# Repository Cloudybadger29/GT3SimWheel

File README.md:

# Custom GT3 Sim Racing Steering Wheel

A project with custom CAD mechanical assembly, 3D printable modular enclosures and ergonomic grips, CNC-machined structural faceplate, integrated magnetic dual-paddle shifters with microswitches, and a custom diode-matrix carrier PCB designed for manual through-hole soldering.

---

## Project Overview

This project is a **GT3 Sim Racing Wheel** engineered for PC sim racing platforms (iRacing, Assetto Corsa Competizione, rFactor 2).

The project is currently in the **detailed engineering and design verification phase**:
- **Mechanical Design (CAD)**: Conceptualized and surfaced initially in **Autodesk Fusion**, then transitioned to **Dassault Systèmes SolidWorks** for assembly modeling and to follow industry standards.
- **Manufacturing Strategy (Planned)**: Hybrid build pairing a rigid CNC-milled structural front plate with 3D-printed modular grips, rear electronics housing, and structural spacer components.
- **Electronics & ECAD (In Progress)**: Custom carrier backplane currently being laid out in **KiCad EDA** around an ATmega32U4 controller, integrating anti-ghosting switching diodes and through-hole solder pads planned for manual assembly.
- **Shifter Subassembly**: Dual-action magnetic paddle units driven by high-reliability Omron microswitches.

*Note: All components are currently modeled in CAD/ECAD. Physical manufacturing and component sourcing will begin once the PCB layout is complete.*

---

## Media & Renders

| Isometric Assembly | Exploded CAD View |
| :---: | :---: |
|  |  |

| Rear & Paddle Assembly | Custom PCB Carrier (KiCad 3D) |
| :---: | :---: |
|  |  |

---

## Key Engineering Points

### 1. Mechanical Design & Manufacturing
- **CNC Structural Faceplate**: A rigid custom CNC-machined front plate designed to withstand high force-feedback torque loads from direct-drive wheelbases without chassis deflection.
- **3D Printing**: All enclosures, grip bodies, and mounting spacers will be 3D printed.
- **Two-Piece Modular Grips**: Split-shell hand grips which can be easily replaced and bolt securely through the faceplate using countersunk M5 hardware.
- **Standard Hub Pattern**: Integrated Moza ESR wheel bolt pattern allowing direct fitment to only the quick release on the Moza ESR Quick Release. Adapters between bolt patterns are widespread.

### 2. Dual-Paddle Magnetic Shifters
- **Actuation**: Integrated 8×3mm magnets give crisp, tactile snap-action return.
- **Sensors**: **Omron D2FC-F-7N** microswitches rated for high-cycle reliability and responsive shift registration.
- **Dual-Paddle Geometry**: Upper and lower paddles allow independent assignment (gear up/down plus secondary functions).

### 3. PCB & Electrical Design (In Design)
- **ECAD Tool**: Schematic capture and board layout in **KiCad EDA**.
- **Microcontroller**: Arduino Pro Micro footprint (ATmega32U4, 5V/16MHz) for native USB HID gamepad capabilities.
- **Assembly Plan**: Through-hole layout designed for precision hand soldering, featuring clearly labeled reference silk screens for components and leaded DO-35 diodes.
- **Ghosting-Free Diode Matrix**: Fast-switching 1N4148 diodes isolate each switch input to prevent crosstalk during simultaneous multi-button presses.
- **Inputs Supported**:
  - 10x PBS-33B momentary pushbuttons
  - 4x Omron D2FC-F-7N paddle microswitches
  - 2x KY-040 rotary encoders (for in-race TC, ABS, or brake-bias trim)
- **Central Pass-Through**: Custom clearance holes routed into the PCB matching the PCD wheelbase bolt circle.

---

## Exploded Assembly Breakdown

The mechanical stack consists of:
1. **Front Split Grips**: Ergonomically shaped front halves fastened with countersunk M5 bolts.
2. **Faceplate Controls**: 10x PBS-33B pushbuttons and 2x KY-040 rotary encoder shafts.
3. **CNC Front Faceplate**: Central load-bearing chassis with countersunk and clearance bores.
4. **Rear Split Grips**: Rear grip shells with internal captive nut pockets.
5. **Back Housing & Spacer**: Houses the custom PCB and internal wiring harness.
6. **Dual Paddle Units**: Dual magnetic microswitch shifters bolted to the rear plate using M2.5/M2 hardware.

---

## Planned Bill of Materials (BOM)

### Fasteners & Hardware

| Category | Type | Specification | Length | Qty | Target Application |
| :--- | :--- | :---: | :---: | :---: | :--- |
| **Screw** | Countersunk | M5 | 35mm | 10 | Main grip retention / faceplate clamp |
| **Screw** | Countersunk | M5 | TBD | 6 | Quick-release / hub mounting |
| **Screw** | Socket Head / Regular | M5 | 22mm | 8 | Main enclosure assembly |
| **Screw** | Socket Head / Regular | M3 | 50mm | 2 | Paddle shifter pivots |
| **Screw** | Socket Head / Regular | M2.5 | 12mm | 8 | Shifter bracket mounts |
| **Screw** | Socket Head / Regular | M2.5 | 10mm | 8 | Shifter brackets |
| **Screw** | Socket Head / Regular | M2 | 10mm | 8 | Omron microswitch mounts |
| **Nut** | Standard Hex / Lock | M5 | — | 24 | M5 screw fastening |
| **Nut** | Standard Hex / Lock | M3 | — | 2 | M3 screw fastening |
| **Nut** | Standard Hex / Lock | M2.5 | — | 16 | M2.5 screw fastening |
| **Nut** | Standard Hex / Lock | M2 | — | 8 | M2 microswitch retention |

### Electronics, Switches & Custom Parts

| Component | Part / Spec | Qty | Notes / Sourcing |
| :--- | :---: | :---: | :--- |
| **Structural Faceplate** | Custom CNC'd front plate | 1 | CNC milled (Aluminum / Carbon Fiber) |
| **Enclosures & Grips** | 3D Printed Components | — | Additive manufacturing (PETG / PLA) |
| **Custom Carrier PCB** | KiCad 2-layer custom board | 1 | In design; planned for manual hand-soldering |
| **Microcontroller** | Arduino Pro Micro (ATmega32U4) | 1 | 5V / 16MHz native USB HID |
| **Tactile Buttons** | PBS-33B Momentary Switches | 10 | Faceplate controls |
| **Shifter Switches** | Omron D2FC-F-7N Microswitches | 4 | Paddle shifter actuation |
| **Rotary Encoders** | KY-040 Encoders | 2 | Real-time ABS / TC / Brake Bias tuning |
| **Magnets** | N52 Neodymium Discs | 4 | 8×3mm magnetic snap return for shifters |
| **Switching Diodes** | 1N4148 DO-35 | 14+ | Matrix anti-ghosting |

---

## Engineering Status & Next Steps

- [x] Mechanical 3D CAD modeling & assembly (Fusion ➔ SolidWorks for industry-standard workflow)
- [ ] Complete routing, silkscreen, and design rule checks (DRC) on the KiCad PCB
- [ ] Order custom PCB prototype batch and BOM components
- [ ] 3D print grip shells, rear electronics housing, internal spacers, and tester faceplate 
- [ ] Order the faceplate for CNC machining
- [ ] Hand-solder PCB components (Pro Micro, diodes, wiring headers)
- [ ] Develop and test USB HID gamepad firmware for ATmega32U4
- [ ] Assembly and calibration
---

## Tools & Environments Used

- **Mechanical CAD**: Autodesk Fusion (initial concepting & surfacing) ➔ Dassault Systèmes SolidWorks (assembly & industry standards)
- **ECAD / PCB Layout**: KiCad EDA

---

## Author, Contact and Credits

- **Designer & Builder**: [Zeeshan Ahmed]((https://github.com/Cloudybadger29))
- **Project Repository**: [GitHub Repo Link](https://github.com/Cloudybadger29/GT3SimWheel)
- **Double Paddle Shifter Designer**: [Joshua van der Voort](https://www.printables.com/@JoshuavanderV_932900)

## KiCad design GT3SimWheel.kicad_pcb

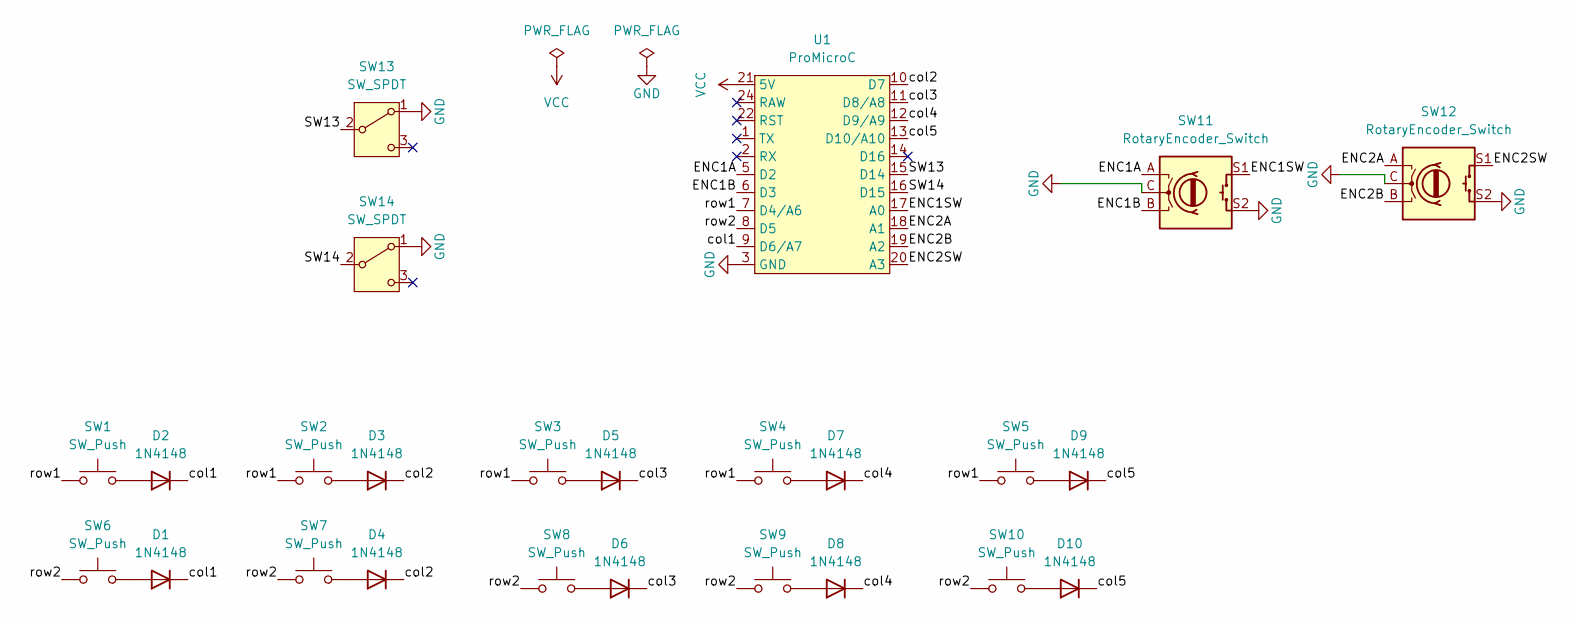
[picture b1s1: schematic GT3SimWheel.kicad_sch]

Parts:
D1, D2, D3, D4, D5, D6, D7, D8, D9, D10: 1N4148; D_DO-35_SOD27_P7.62mm_Horizontal
SW1, SW2, SW3, SW4, SW5, SW6, SW7, SW8, SW9, SW10: SW_Push; JST_PH_S2B-PH-K_1x02_P2.00mm_Horizontal
SW11, SW12: RotaryEncoder_Switch; RotaryEncoder_Alps_EC11E-Switch_Vertical_H20mm
SW13, SW14: SW_SPDT; PinHeader_1x03_P2.54mm_Vertical
U1: ProMicroC

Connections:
/<NO NET>: D8.2 (A), SW9.2
/ENC1A: SW11.A, U1.5 (D2)
/ENC1B: SW11.B, U1.6 (D3)
/ENC1SW: SW11.S1, U1.17 (A0)
/ENC2A: SW12.A, U1.18 (A1)
/ENC2B: SW12.B, U1.19 (A2)
/ENC2SW: SW12.S1, U1.20 (A3)
/SW13: SW13.2 (B), U1.15 (D14)
/SW14: SW14.2 (B), U1.16 (D15)
/col1: D1.1 (K), D2.1 (K), U1.9 (D6/A7)
/col2: D3.1 (K), D4.1 (K), U1.10 (D7)
/col3: D5.1 (K), D6.1 (K), U1.11 (D8/A8)
/col4: D7.1 (K), D8.1 (K), U1.12 (D9/A9)
/col5: D9.1 (K), D10.1 (K), U1.13 (D10/A10)
/row1: SW1.1, SW2.1, SW3.1, SW4.1, SW5.1, U1.7 (D4/A6)
/row2: SW6.1, SW7.1, SW8.1, SW9.1, SW10.1, U1.8 (D5)
GND: SW11.C, SW11.S2, SW12.C, SW12.S2, SW13.1 (A), SW14.1 (A), U1.3 (GND), U1.4 (GND), U1.23 (GND)
unnamed: D1.2 (A), SW6.2
unnamed: D2.2 (A), SW1.2
unnamed: D3.2 (A), SW2.2
unnamed: D4.2 (A), SW7.2
unnamed: D5.2 (A), SW3.2
unnamed: D6.2 (A), SW8.2
unnamed: D7.2 (A), SW4.2
unnamed: D9.2 (A), SW5.2
unnamed: D10.2 (A), SW10.2
VCC: U1.21 (5V)

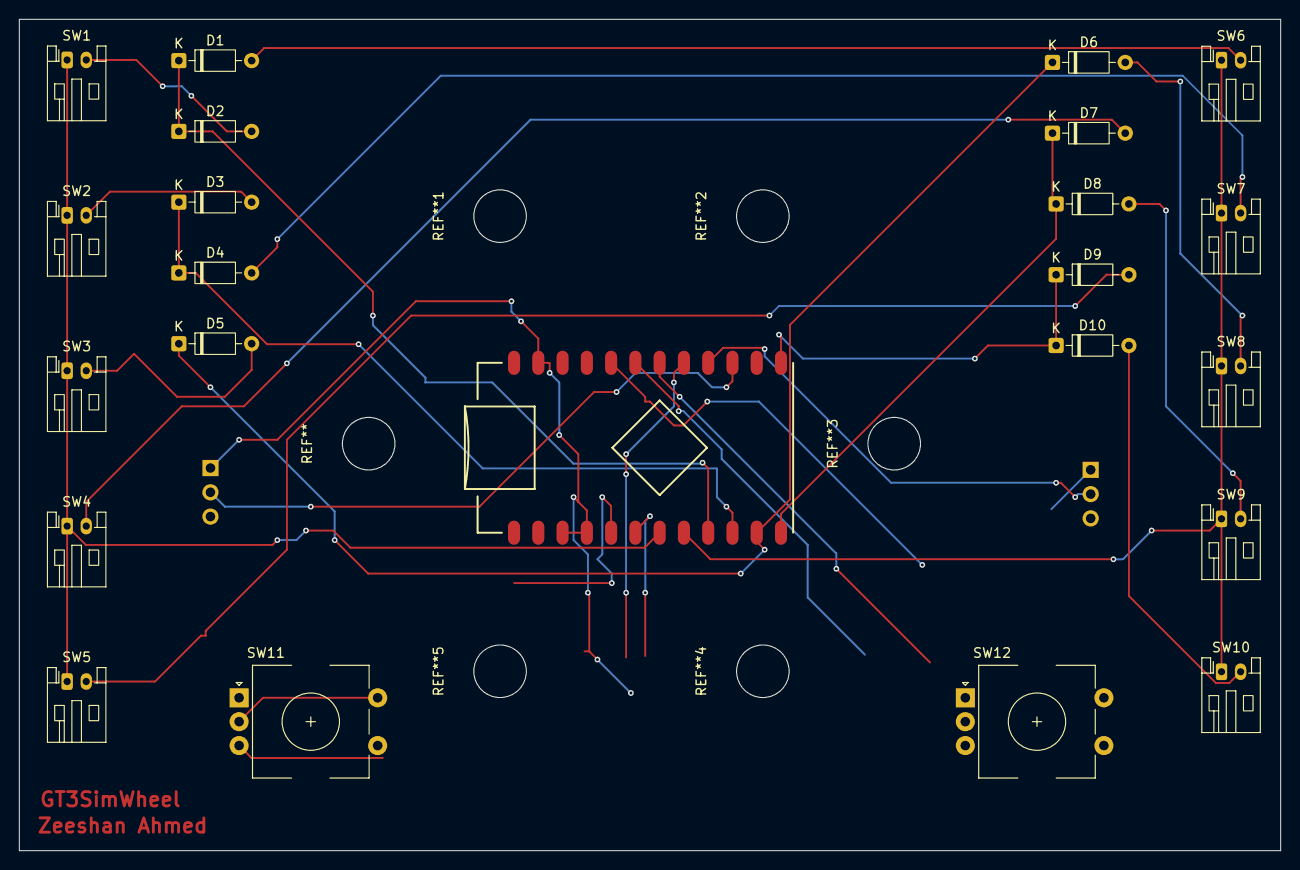
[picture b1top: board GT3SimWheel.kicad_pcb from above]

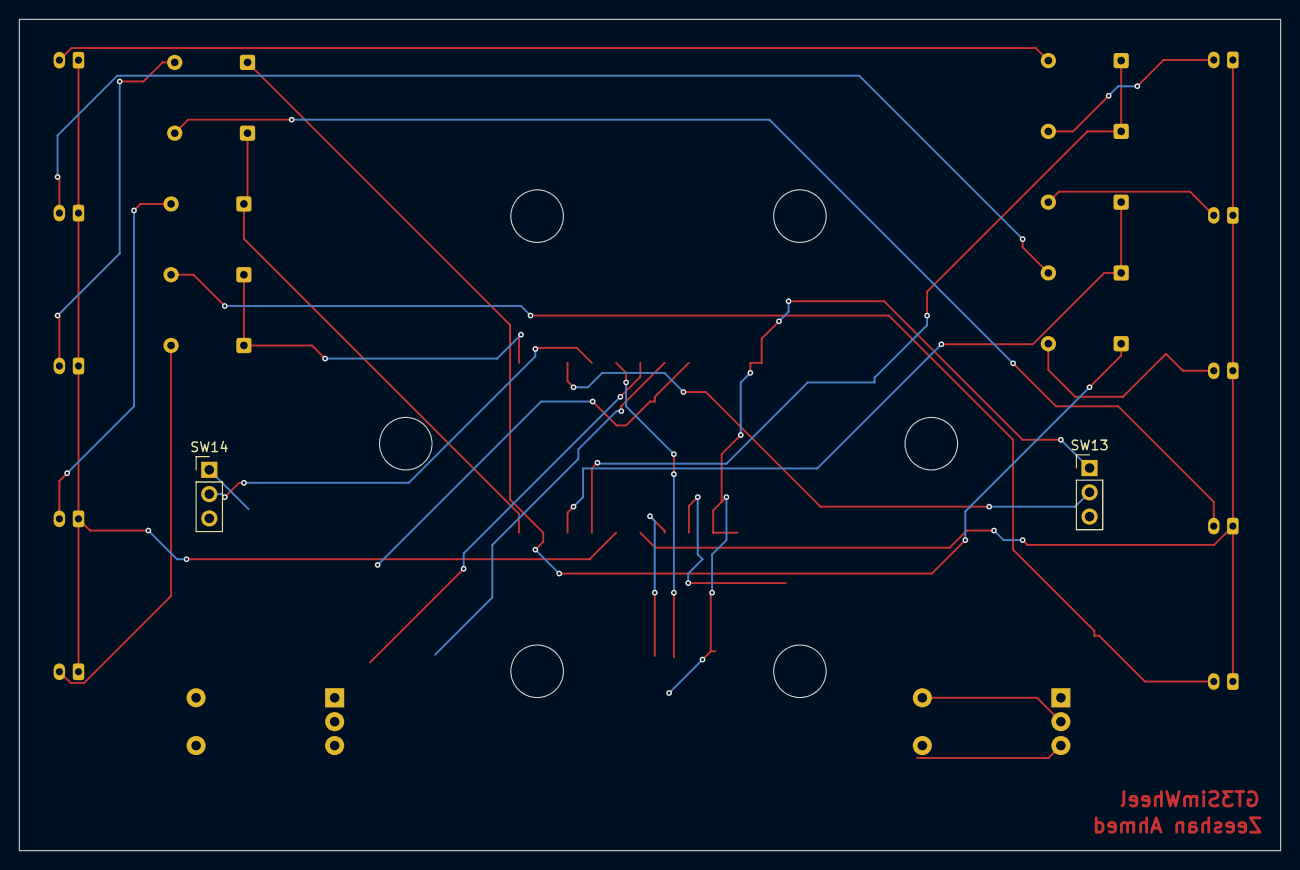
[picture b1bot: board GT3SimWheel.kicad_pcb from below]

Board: 2 copper layers, 132.0 x 87.0 mm, 25 parts (2 on the bottom side), 26 nets.
